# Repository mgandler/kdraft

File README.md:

# kdraft

Fabrication and assembly drawings for KiCad boards: a native desktop editor
and a command-line tool, written in Rust. kdraft reads a `.kicad_pcb`, lays
out a drawing set (fabrication view, assembly views, drill drawing, drill
table, layer stack, bill of materials, notes, dimensions, callouts) on
KiCad drawing sheets and exports it as PDF, SVG or PNG. The model is
Altium Draftsman; the target is KiCad 9 and 10.

> **Written entirely by AI agents.** Every line of code, every test and
> all documentation in this repository, this file included, was written by
> AI coding agents (Anthropic's Claude). No code was written by hand. A
> person specified the tool, made the decisions, ran it on real boards and
> reported what was wrong. See [How it was written](#how-it-was-written).

## A short tour

Callouts and dimensions snap to pads, holes and outline points and stay
attached to the board:

Align, distribute, reorder pages:

Layer colours and themes:

The board in the animations is the
[RoyalBlue54L Feather](https://www.crowdsupply.com/lords-boards/royalblue54l-feather)
by Lord's Boards, one of KiCad's demo projects (see [Credits](#credits)).
They were recorded with the editor's headless mode on a machine without
KiCad, so the views are kdraft's own preview drawn from the board file;
with `kicad-cli` installed the views are KiCad's plots.
`scripts/readme-gifs/record.py` records them again.

An exported page (test board `fixtures/kicad10-minimal.kicad_pcb`, also
drawn without KiCad):

## Status

Version 0.1.0, early. It is used on one real four-layer board (350
footprints) with KiCad 10.0.8 on Windows; expect rough edges.

| | |
| --- | --- |
| Run by a person | Windows with KiCad 10.0.8: the editor, plotted views (they match the board to 0.0000 mm at the pads), schematic BOM, 3D renders |
| Builds and passes its tests, editor window not tried | Linux |
| Not tried | macOS; KiCad 9.0.x (`kicad-cli`); board files written by KiCad 9 are parsed and tested |
| Units | millimetres only |

Not done yet: angular dimensions, ellipses, dragging table column widths,
a layer legend item, detail and section views, DXF export, a KiCad IPC
plugin (cross-probing), a size limit for the cache, UI languages other
than English. `docs/STATUS.md` lists what works and what has been checked
by a person; `docs/PLAN.md` holds the architecture and the roadmap.

## What it does

- **Pages and sheets.** Any number of pages, each on KiCad's default
  drawing sheet, the project's sheet or your own `.kicad_wks`. Pages are
  reordered by dragging; items align, distribute and snap (0.5 mm grid,
  anchors of other items).
- **Views of the board.** Fabrication, assembly top and bottom (reference
  designators placed without overlaps), drill drawing with one symbol per
  tool, single-layer views, and 3D views rendered by KiCad. With
  `kicad-cli` installed, views are KiCad's own plots; without it, kdraft
  draws a preview from the board file.
- **Tables.** Drill table (grouped like KiCad's drill files), layer stack,
  bill of materials from the schematic (`kicad-cli sch export bom`) or,
  without a schematic, from the board.
- **Annotations.** Linear, ordinate, radius and diameter dimensions with
  tolerances, attached to board features, so they follow the view when it
  moves or the board changes;
  numbered notes; callouts (free numbers, note, BOM item, designator);
  lines, polylines, rectangles and multi-line text; colours and line
  styles for all of them.
- **Layer colours.** Per view or per document: black, greyscale, KiCad's
  built-in themes (also adapted for white paper) or a colour theme
  imported from KiCad.
- **Placement links.** A view can follow another view's position, scale,
  rotation and colours across pages. "Layer pages" creates one page per
  copper layer, all at the same place.
- **Checks.** `kdraft check` and the editor report broken anchors, a
  board that changed since the drawing was made, overflowing tables,
  overlaps and designators that could not be placed.
- **One command table.** The editor's menus, the command palette (Ctrl+K)
  and `kdraft cmd run` use the same 100 or so commands, all undoable, so
  everything the editor does can be scripted.

kdraft never writes into your KiCad project: `kicad-cli` runs on a private
copy of the project files in a cache folder.

## Requirements

To build:

- **Rust** 1.92 or newer, stable toolchain, from <https://rustup.rs>
  (developed with 1.97). On Windows this is the MSVC toolchain; rustup
  asks for the Visual Studio C++ Build Tools if they are missing.
- **Git**.
- A few GB of free disk space for the build folder. No other libraries
  or SDKs: all dependencies are Rust crates that Cargo downloads.

To run:

- **Windows 10 or 11** (the target platform), with a graphics driver that
  provides OpenGL 2 or newer. For remote desktops and virtual machines
  without OpenGL there is a DirectX 12 / Vulkan build, see below.
- **KiCad 9 or 10**, optional but recommended. `kicad-cli` from the KiCad
  installation is needed for plot-exact views, the schematic BOM and 3D
  views. It is found on `PATH` or in `C:\Program Files\KiCad\<version>\bin`;
  another location can be set under File > Settings.

## Build

```
git clone https://github.com/mgandler/kdraft.git
cd kdraft
cargo build --release -p kdraft-ui -p kdraft-cli
```

This produces `target\release\kdraft-gui.exe` (the editor) and
`target\release\kdraft.exe` (the command-line tool). The first build
downloads and compiles a few hundred crates and takes several minutes.

Editor for machines without OpenGL (DirectX 12 / Vulkan through wgpu):

```
cargo build --release -p kdraft-ui --no-default-features --features wgpu
```

## Run

The editor, empty, with a board or with a drawing:

```
cargo run --release -p kdraft-ui --bin kdraft-gui
cargo run --release -p kdraft-ui --bin kdraft-gui -- path\to\board.kicad_pcb
cargo run --release -p kdraft-ui --bin kdraft-gui -- path\to\drawing.kdraft
```

Opening a `.kicad_pcb` creates a new drawing set; Save writes it next to
the board as `<board>.kdraft`. Layout, tools and shortcuts are described
in `docs/GUI.md`.

The same from the command line, with the test board in this repository:

```
cargo run --release -p kdraft-cli -- doc new fixtures/kicad10-minimal.kicad_pcb -o demo.kdraft
cargo run --release -p kdraft-cli -- check demo.kdraft
cargo run --release -p kdraft-cli -- export demo.kdraft -o demo.pdf
```

## Command line

```
kdraft inspect <board.kicad_pcb> [--json]
kdraft drill-table <board.kicad_pcb> [--json]
kdraft diff <old.kicad_pcb> <new.kicad_pcb> [--json]   # exit 1 if changed
kdraft sexpr-check <file>                              # byte-exact round trip
kdraft doc new <board.kicad_pcb> -o out.kdraft [--force]
kdraft doc validate <file.kdraft>
kdraft export <file.kdraft> -o out.pdf [--format pdf|svg|png] [--dpi N]
              [--kicad-cli PATH | --no-kicad-cli] [--sheet-from-kicad-cli]
kdraft check <file.kdraft> [--json]                    # exit 0 clean, 1 warnings, 2 errors
kdraft cmd list [--json]                               # the commands the editor uses
kdraft cmd run <file.kdraft> --do NAME [--args JSON] [--do ...] [-o out.kdraft]
kdraft settings path|show|reset
kdraft settings set <kicad_cli|define_vars|cache_dir|documents.KEY> <value>
kdraft settings palettes list
kdraft settings palettes import-kicad <theme.json> [--name N] [--no-adapt]
kdraft kicad list                                      # installs found, the one in use
```

Settings are shared by the editor and the command line and stored in
`%APPDATA%\kdraft\settings.json`; `--settings FILE` or `KDRAFT_SETTINGS`
select another file. `kicad-cli` is taken from `--kicad-cli`, else
`KDRAFT_KICAD_CLI`, else the setting, else the newest installation found.

Example: move page 1 to the end and left-align two items.

```
kdraft cmd run d.kdraft --do page.move --args "{\"from\": 0, \"to\": 2}" --do select.set --args "{\"ids\": [\"<id1>\", \"<id2>\"]}" --do layout.align --args "{\"mode\": \"left\"}"
```

## Development

```
cargo test --workspace
cargo fmt --all -- --check
cargo clippy --workspace --all-targets -- -D warnings
```

- `scripts/fetch-fixtures.sh` (bash or Git Bash) downloads KiCad's demo
  boards into `fixtures-ext/`; tests that use them skip themselves when
  the folder is absent.
- Tests that need a real `kicad-cli` are `#[ignore]`d and read
  `KDRAFT_KICAD_CLI`.
- Golden images of the renderer are regenerated with
  `KDRAFT_UPDATE_GOLDEN=1 cargo test -p kdraft-render`.
- `kdraft-gui --screenshot out.png [--script steps.json] file` renders
  the editor without a window. The animations above are made this way by
  `scripts/readme-gifs/record.py` (Python 3 with Pillow, ffmpeg);
  `scripts/readme-gifs/capture.cmd` captures the frames on Windows
  without Python.

| Crate | Purpose |
| --- | --- |
| `kdraft-sexpr` | Lossless S-expression reader and writer for KiCad files |
| `kdraft-board` | Board model: outline, footprints, holes, drill table, stackup, BOM |
| `kdraft-source` | Finding and running `kicad-cli`, cache, settings, KiCad colour themes |
| `kdraft-plot` | Reading KiCad's SVG plots and fitting them to board coordinates |
| `kdraft-sheet` | Drawing sheets (`.kicad_wks`) and project settings (`.kicad_pro`) |
| `kdraft-doc` | The `.kdraft` document: pages, views, tables, annotations, styles, links |
| `kdraft-layout` | Designator placement, dimension geometry, text layout |
| `kdraft-render` | Display list and output: PDF, SVG, PNG |
| `kdraft-engine` | Session, commands with undo, snapping, checks |
| `kdraft-ui` | The editor `kdraft-gui` (egui) |
| `kdraft-cli` | The command-line tool `kdraft` |

## Licence

kdraft is free software under the **GNU General Public License, version 3
or later** (`LICENSE`). Copyright (C) the kdraft authors.

## Credits

### Code and data taken from other projects

These are part of this repository. `NOTICE` and the `NOTICE` files under
`assets/` carry the full notices and licence texts.

| From | What | Where in kdraft | Licence |
| --- | --- | --- | --- |
| [KiCad](https://www.kicad.org) ([source](https://gitlab.com/kicad/code/kicad), tags 9.0.9 and 10.0.8) | The default drawing sheet, copied verbatim from `common/drawing_sheet/drawing_sheet_default_description.cpp` | `assets/sheets/default.kicad_wks` | GPL-2.0-or-later |
| KiCad (tag 10.0.8) | Board layer colours of the built-in themes "KiCad Default" and "KiCad Classic", from `common/settings/builtin_color_themes.h` and `common/gal/color4d.cpp`; the colour theme file format follows `common/settings/color_settings.cpp` | `crates/kdraft-doc/src/palette.rs`, `crates/kdraft-source/src/kicad_theme.rs` | GPL-3.0-or-later |
| [FigCraft](https://github.com/storytold/figcraft) (commit c01d391) | Structure of the UI theme tokens, the pixel-hinting icon painter helper, and the widget set and its interaction model (number fields with scrub and nudge, segmented control, section headers, drag ghost, inline rename). Colours, icons and the rest of the code are kdraft's own. | `crates/kdraft-ui/src/theme.rs`, `icons.rs`, `widgets.rs` | MIT OR Apache-2.0, used under MIT |
| [IBM Plex Sans](https://github.com/IBM/plex) 3.006 | Regular and Bold font files, embedded in the program and in exported PDFs | `assets/fonts/` | SIL Open Font License 1.1 |

Recorded output of KiCad used by the tests: the `kicad-cli` 10.0.8 help
texts in `fixtures/kicad-cli/` and the SVG plots in
`fixtures/kicad-cli-svg/`, which `kicad-cli` produced from kdraft's own
test board. KiCad's demo boards are downloaded by
`scripts/fetch-fixtures.sh` and are not part of this repository.

The animations in this file show drawings of the **RoyalBlue54L Feather**
by Lord's Boards, licensed under the CERN Open Hardware Licence
Version 2 - Permissive (CERN-OHL-P v2). The design files are in KiCad's
source tree under `demos/royalblue54L_feather` (tag 10.0.8) and are not
part of this repository.

### Libraries

Linked as Cargo dependencies, not copied. The direct ones:

| Library | Used for | Licence |
| --- | --- | --- |
| [egui, eframe](https://github.com/emilk/egui) 0.37, with winit and glow (optionally wgpu) | The editor's user interface and window | MIT OR Apache-2.0 (winit: Apache-2.0; glow: MIT OR Apache-2.0 OR Zlib) |
| [krilla](https://github.com/LaurenzV/krilla) 0.8 | Writing PDF | MIT OR Apache-2.0 |
| [tiny-skia](https://github.com/linebender/tiny-skia) 0.12 | PNG output and the editor's page pictures | BSD-3-Clause |
| [ttf-parser](https://github.com/harfbuzz/ttf-parser) 0.25 | Font metrics and outlines | MIT OR Apache-2.0 |
| [roxmltree](https://github.com/RazrFalcon/roxmltree) 0.21 | Reading KiCad's SVG plots | MIT OR Apache-2.0 |
| [rfd](https://github.com/PolyMeilex/rfd) 0.18 | Native file dialogs | MIT |
| [clap](https://github.com/clap-rs/clap) 4 | Command-line parsing | MIT OR Apache-2.0 |
| [serde, serde_json](https://github.com/serde-rs/serde) 1 | Settings, command arguments | MIT OR Apache-2.0 |
| [blake3](https://github.com/BLAKE3-team/BLAKE3) 1 | Cache keys, board fingerprints | CC0-1.0 OR Apache-2.0 |
| [uuid](https://github.com/uuid-rs/uuid), [thiserror](https://github.com/dtolnay/thiserror), [anyhow](https://github.com/dtolnay/anyhow) | Identifiers, error types | MIT OR Apache-2.0 |
| [proptest](https://github.com/proptest-rs/proptest), [tempfile](https://github.com/Stebalien/tempfile), egui_kittest | Tests only | MIT OR Apache-2.0 |

`Cargo.lock` pins the complete dependency tree; `cargo tree` prints it.

### Ideas, no code

- **Altium Draftsman**: the kind of document, its views, tables and
  annotations.
- [PdfCraft](https://github.com/storytold/pdfcraft): one engine behind
  editor and command line, a command table that describes its own
  arguments, a pages panel with undoable page moves.
- [CADCraft](https://github.com/storytold/cadcraft): dimensions that stay
  attached to geometry, object snaps.
- FigCraft: the look and feel of the editor, beyond the adapted files
  listed above.

### How it was written

This project was written completely by AI agents: Anthropic's Claude in
Claude Code, with Claude Opus 5.5 as the implementing agent and Claude
Fable 5.2 planning, reviewing and making small fixes. That covers the
architecture plan, all source code, the tests and the documentation.

The repository starts with a single commit: the 61 commits of the
development before publication were squashed into it. Commit hashes
mentioned in `docs/` refer to that earlier history.

The human part: the idea and the requirements, the decisions (licence,
platform, units, where the BOM comes from), building and running it on
Windows with KiCad 10.0.8 on a real board, and bug reports and feature
requests from that use. What a person has and has not checked is recorded
in `docs/STATUS.md`. Read the code and the output with that in mind.

## Disclaimer

kdraft is an independent project. It is not affiliated with or endorsed
by the KiCad project or Altium. KiCad, Altium and Draftsman are
trademarks of their respective owners.
There is no warranty; check every drawing before it goes to a
manufacturer.

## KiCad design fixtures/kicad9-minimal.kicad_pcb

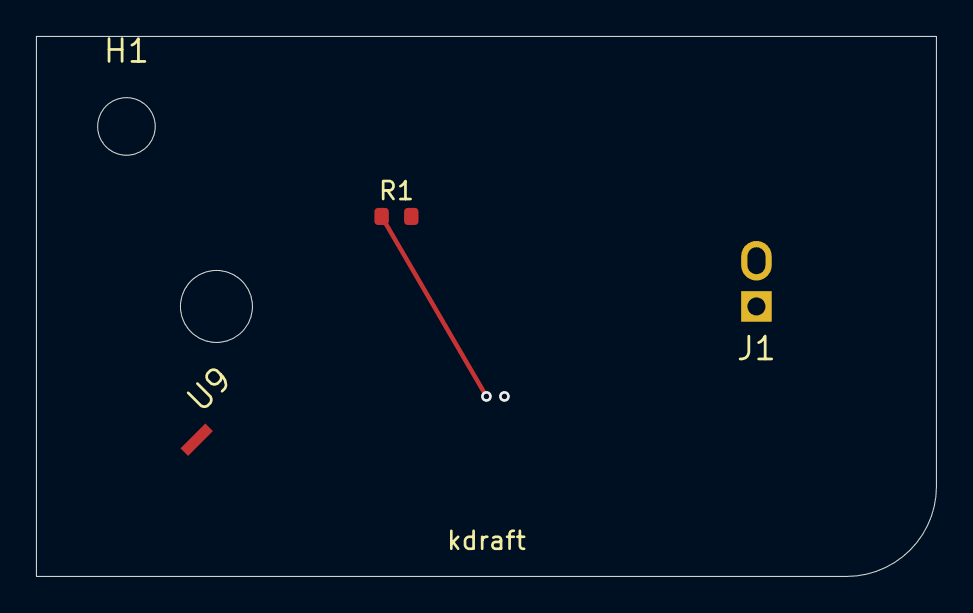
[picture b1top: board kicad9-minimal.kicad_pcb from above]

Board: 2 copper layers, 50.0 x 30.0 mm, 5 parts (1 on the bottom side), 2 nets.

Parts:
C1: 100n; C_0402_1005Metric
H1: MountingHole; MountingHole_3.2mm_M3
J1: Conn_01x02; PinHeader_1x02_P2.54mm_Vertical
R1: 10k; R_0603_1608Metric
U9: LM358; SOIC-8_3.9x4.9mm_P1.27mm

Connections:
GND: C1.2, R1.2
VCC: C1.1, J1.1, R1.1
